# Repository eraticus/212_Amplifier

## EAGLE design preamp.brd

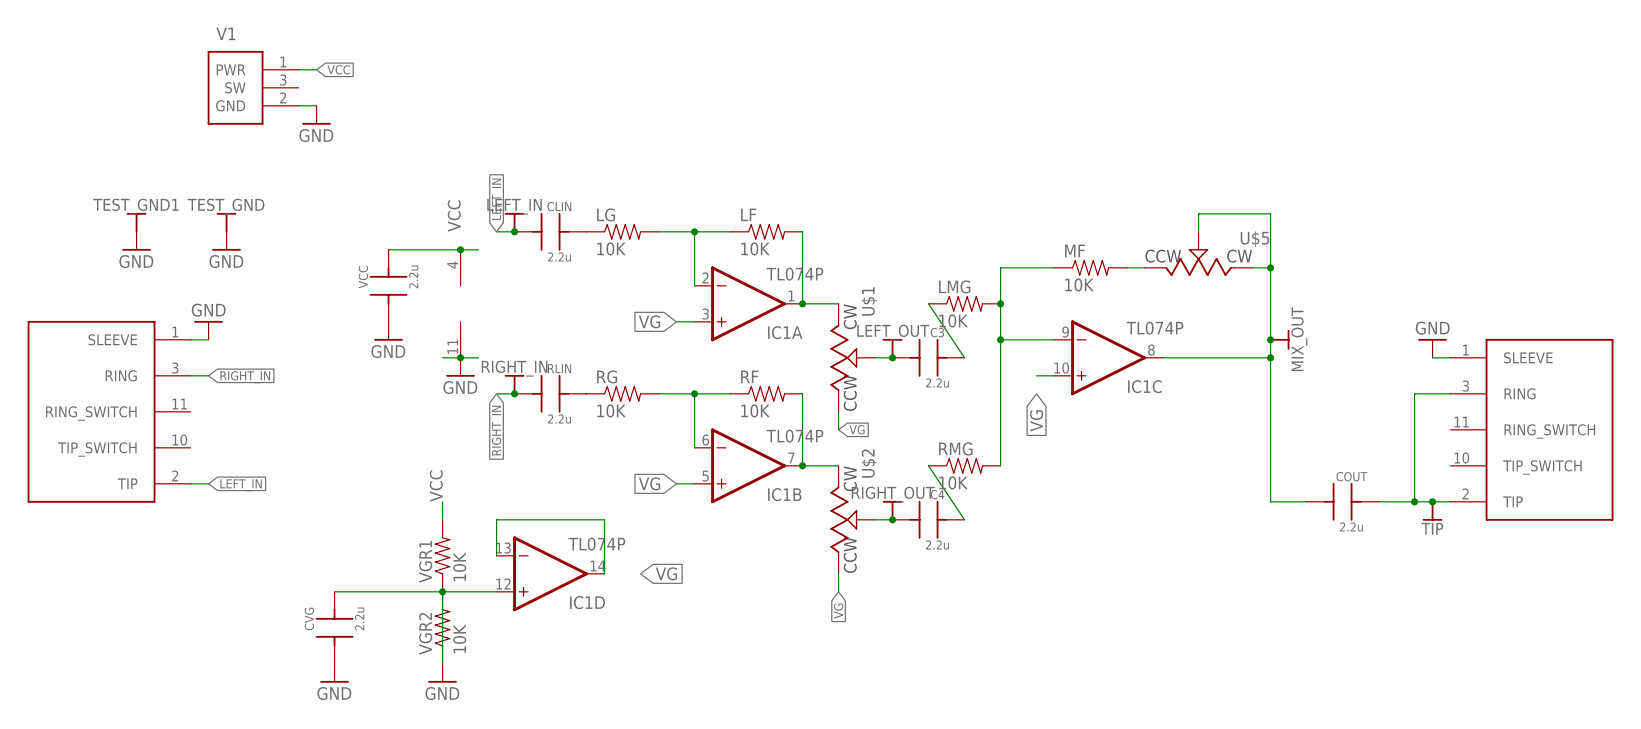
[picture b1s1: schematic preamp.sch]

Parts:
C3, C4: 2.2u; C322
CLIN: 2.2u; C322
COUT: 2.2u; C322
CVG: 2.2u; C322
IC1: TL074P; DIL14
LEFT_IN: TEST_POINTMINIATURE; PLATED_HOLE_1.02MM
LEFT_OUT: TEST_POINTMINIATURE; PLATED_HOLE_1.02MM
LF: 10K; AXIAL-0.4
LG: 10K; AXIAL-0.4
LMG: 10K; AXIAL-0.4
MF: 10K; AXIAL-0.4
MIX_OUT: TEST_POINTMINIATURE; PLATED_HOLE_1.02MM
RF: 10K; AXIAL-0.4
RG: 10K; AXIAL-0.4
RIGHT_IN: TEST_POINTMINIATURE; PLATED_HOLE_1.02MM
RIGHT_OUT: TEST_POINTMINIATURE; PLATED_HOLE_1.02MM
RLIN: 2.2u; C322
RMG: 10K; AXIAL-0.4
TEST_GND, TEST_GND1: TEST_POINTMINIATURE; PLATED_HOLE_1.02MM
TIP: TEST_POINTMINIATURE; PLATED_HOLE_1.02MM
U$1, U$2, U$5: POTENTIOMETER3362P; 3362P
U$3, U$4: AUDIO_5_CONDUCTOR; SJ1-3525N
V1: POWER_JACK; PJ-102AH
VCC: 2.2u; C322
VGR1, VGR2: 10K; AXIAL-0.4

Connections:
GND: CVG.1, IC1.11 (V-), TEST_GND.1, TEST_GND1.1, U$3.1 (SLEEVE), U$4.1 (SLEEVE), V1.2 (GND), VCC.1, VGR2.P$2 (2)
LEFT_IN: CLIN.1, LEFT_IN.1, U$3.2 (TIP)
unnamed: IC1.2 (-IN), LF.P$1 (1), LG.P$2 (2)
unnamed: IC1.6 (-IN), RF.P$1 (1), RG.P$2 (2)
unnamed: IC1.7 (OUT), RF.P$2 (2), U$2.3 (CW)
unnamed: IC1.1 (OUT), LF.P$2 (2), U$1.3 (CW)
unnamed: RG.P$1 (1), RLIN.2
unnamed: CLIN.2, LG.P$1 (1)
unnamed: CVG.2, IC1.12 (+IN), VGR1.P$1 (1), VGR2.P$1 (1)
unnamed: C3.1, LEFT_OUT.1, U$1.2 (WIPER)
unnamed: C3.2, LMG.P$1 (1)
unnamed: C4.2, RMG.P$1 (1)
unnamed: IC1.9 (-IN), LMG.P$2 (2), MF.P$1 (1), RMG.P$2 (2)
unnamed: C4.1, RIGHT_OUT.1, U$2.2 (WIPER)
unnamed: COUT.1, IC1.8 (OUT), MIX_OUT.1, U$5.2 (WIPER), U$5.3 (CW)
unnamed: COUT.2, TIP.1, U$4.2 (TIP), U$4.3 (RING)
unnamed: MF.P$2 (2), U$5.1 (CCW)
RIGHT_IN: RIGHT_IN.1, RLIN.1, U$3.3 (RING)
SW: V1.3 (SW)
VCC: IC1.4 (V+), V1.1 (PWR), VCC.2, VGR1.P$2 (2)
VG: IC1.3 (+IN), IC1.5 (+IN), IC1.10 (+IN), IC1.13 (-IN), IC1.14 (OUT), U$1.1 (CCW), U$2.1 (CCW)

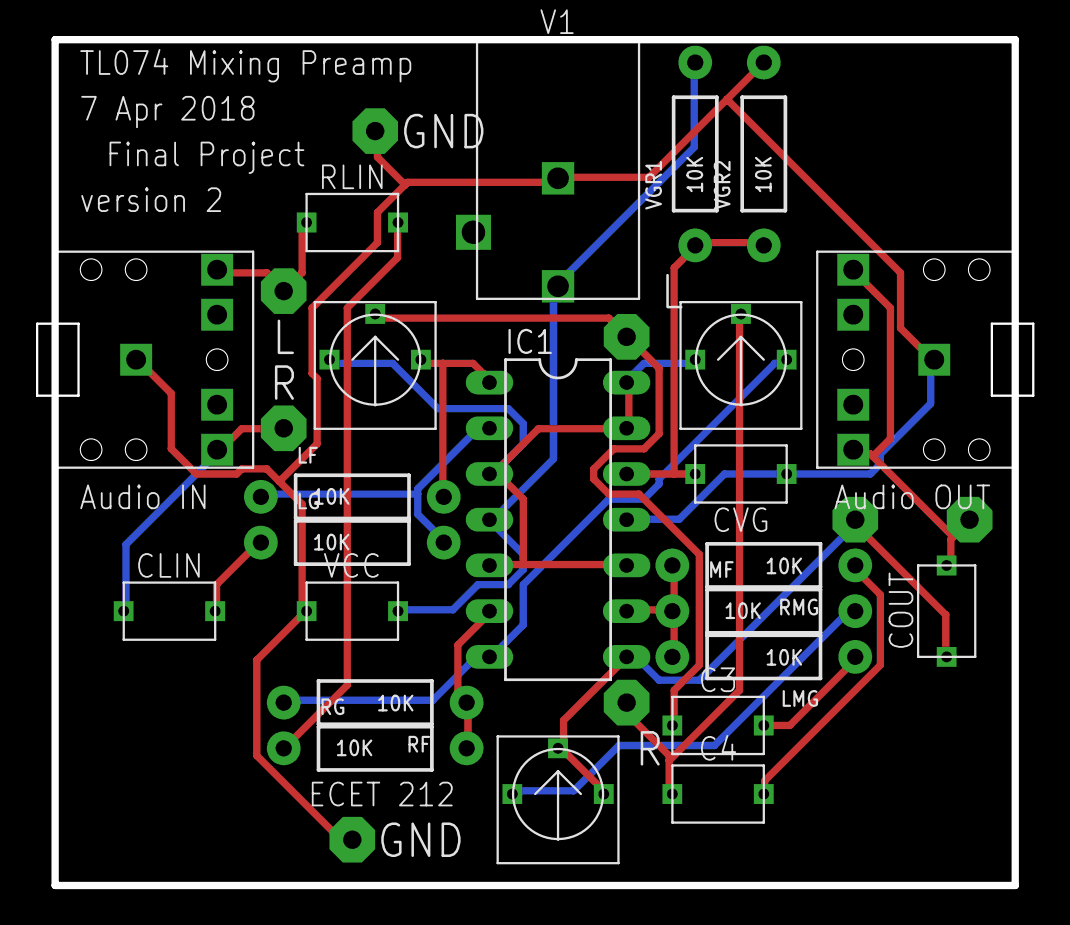
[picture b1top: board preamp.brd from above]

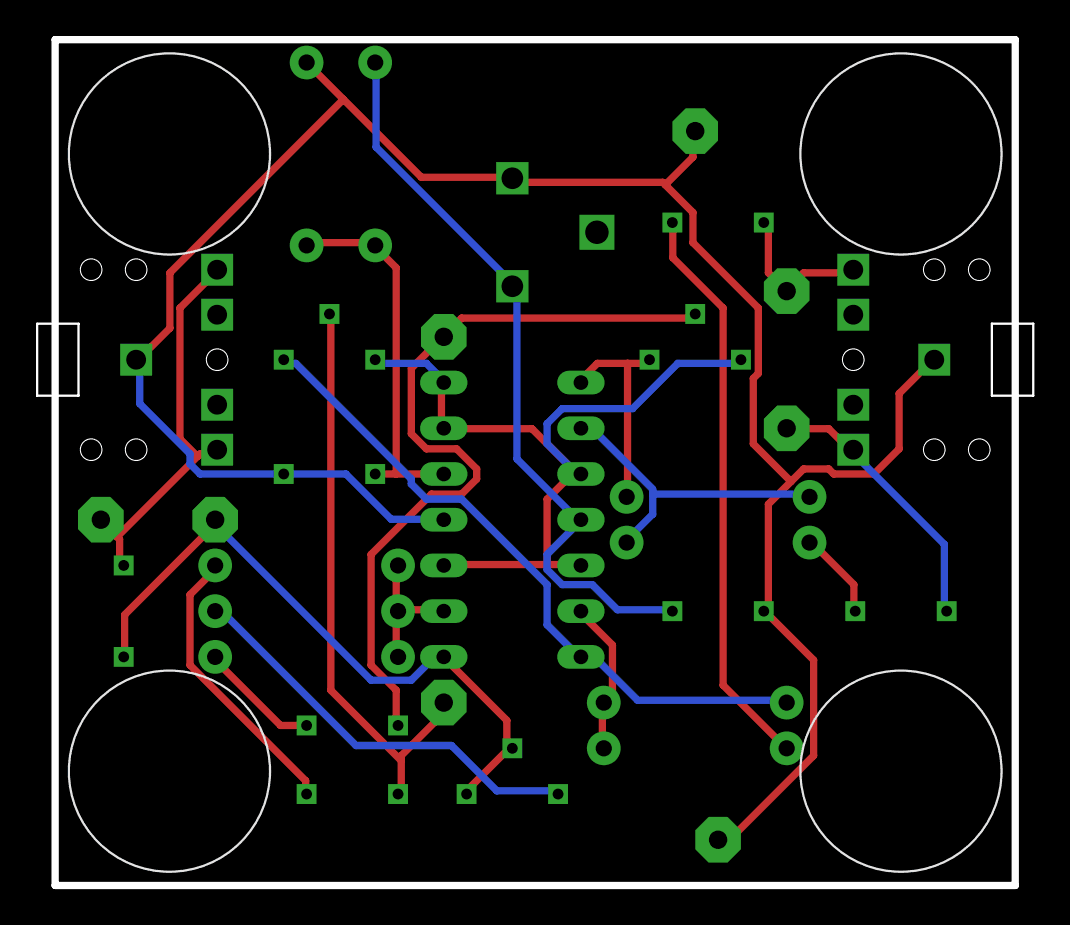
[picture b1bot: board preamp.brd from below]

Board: 2 copper layers, 55.1 x 47.0 mm, 35 parts (4 on the bottom side), 20 nets.

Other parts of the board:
U$7, U$8, U$9, U$10: SJ-5003

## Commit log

2018-03-25 first version of 212 preamplifier circuit
2018-04-07 corrected audio jack drill sizes, added test points.

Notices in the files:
parts and their libraries:
SparkFun-Passives: Licensing: Creative Commons ShareAlike 4.0 International - https://creativecommons.org/licenses/by-sa/4.0
